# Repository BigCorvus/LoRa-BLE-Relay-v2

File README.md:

# LoRa-BLE-Relay-v2
second version of the nRF52840 and SX126x-based communication device intended to run Meshtastic-
This version is in the testing process. Not confirmed working yet.

See fourm discussion https://meshtastic.discourse.group/t/building-for-nrf52-boards/457/62  

The initial 2.0 version:  

Features are: 
- 110x50mm  
- more ground plane for better LoRa RF performance
- low power consumption in receive mode and Bluetooth active: about 20mA for the 30dbm and 10mA for the 22dbm module version  
- nRF52840 module by Waveshare/HolyIOT with native USB bootloader, broken out NFC pins and good Arduino support (Adafruit Core)  
- Ebyte E22 LoRa Modules based on new Semtech SX126x chipsets for 22 or 30dbm and 915,868,433...Mhz frequency bands. 
- Footprint for both the big and the small LoRa module (the boost converter doesn't need to be assembled if the smaller one is used)  
- SD card slot (same card holder as in the Adafruit Adalogger boards  
- On board buzzer  
- GPS connector breaking out RXD and TXD (JST-SH 4-pin) with high-side power cutting option.   
- Many screen options: usual 128x64 OLEDs via I2C or sunlight-readable and power-efficient ST7565R and UC1701X LCD screens via bitbanged 4 line SPI (see BOM for variants)  
- display headers can be expansion headers  
- 3 nav buttons  
- powered from 1 or 2 parallel unprotected 18650 cells (protection circuitry on board)  
- port for external battery or solar charger for concurrent charging  
- battery temperature monitoring/environmental sensing via BME280  
- USB-C connector
- power management via TI fuel gauge IC with optional programmable power cutting option  (selectable via solder jumper, experimental!) 

To do in next version: reverse polarity protection for batteries.

Installation of the Arduino variant: put the variant.h and .cpp in a folder named LoRaBLERelayV2 which has to be created inside the variants folder of the nrf52 core. There you also have boards.txt which you have to extend by the content of the boards.txt inside this repo.

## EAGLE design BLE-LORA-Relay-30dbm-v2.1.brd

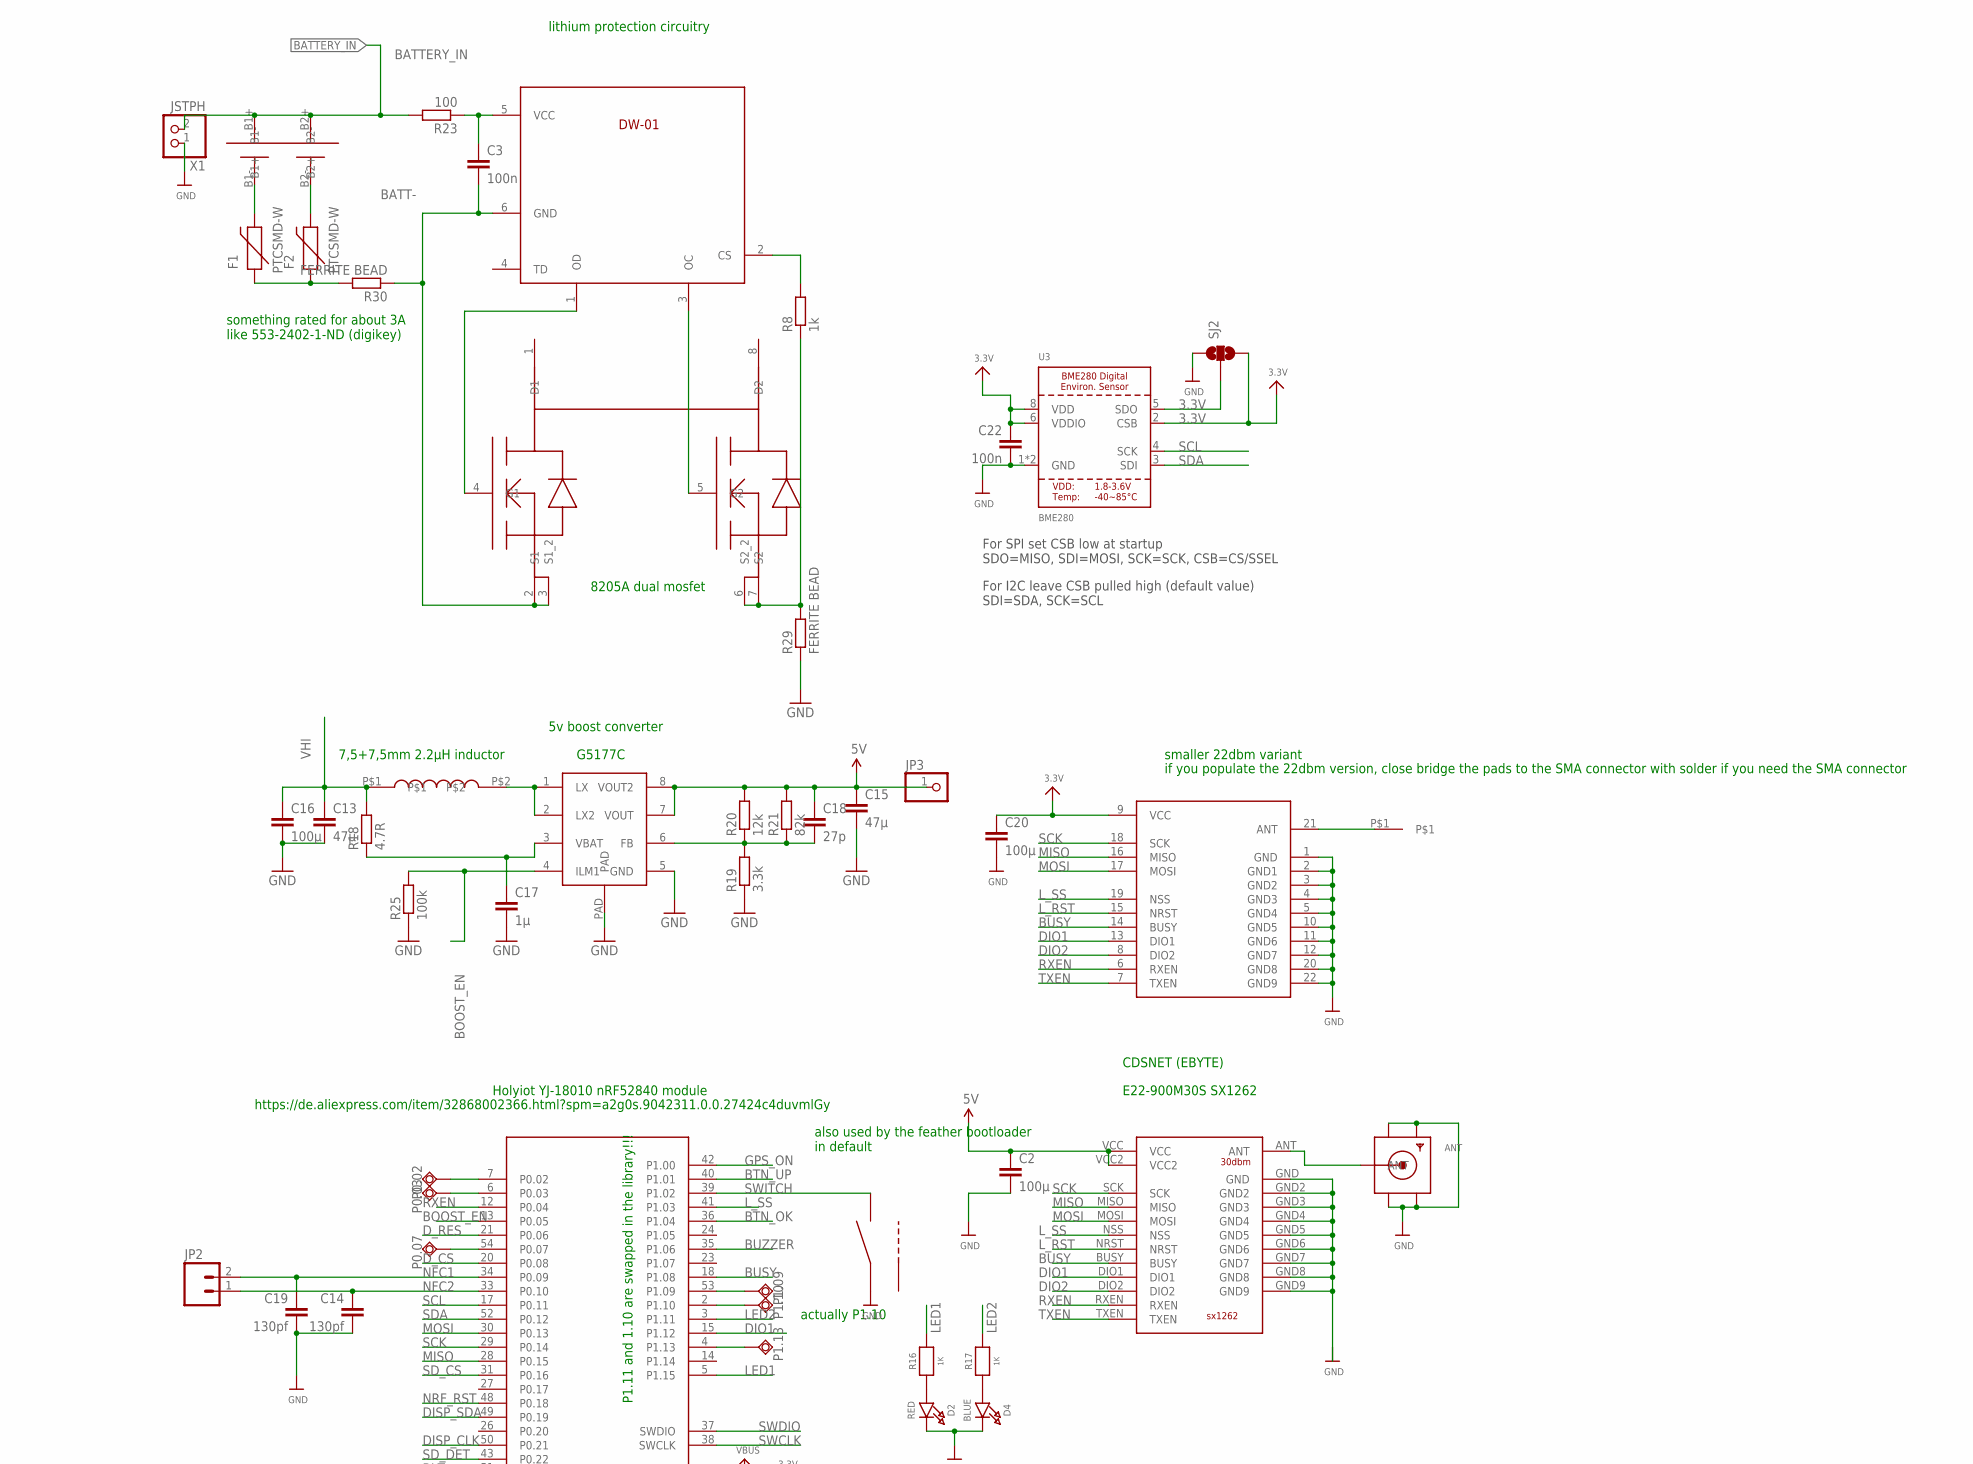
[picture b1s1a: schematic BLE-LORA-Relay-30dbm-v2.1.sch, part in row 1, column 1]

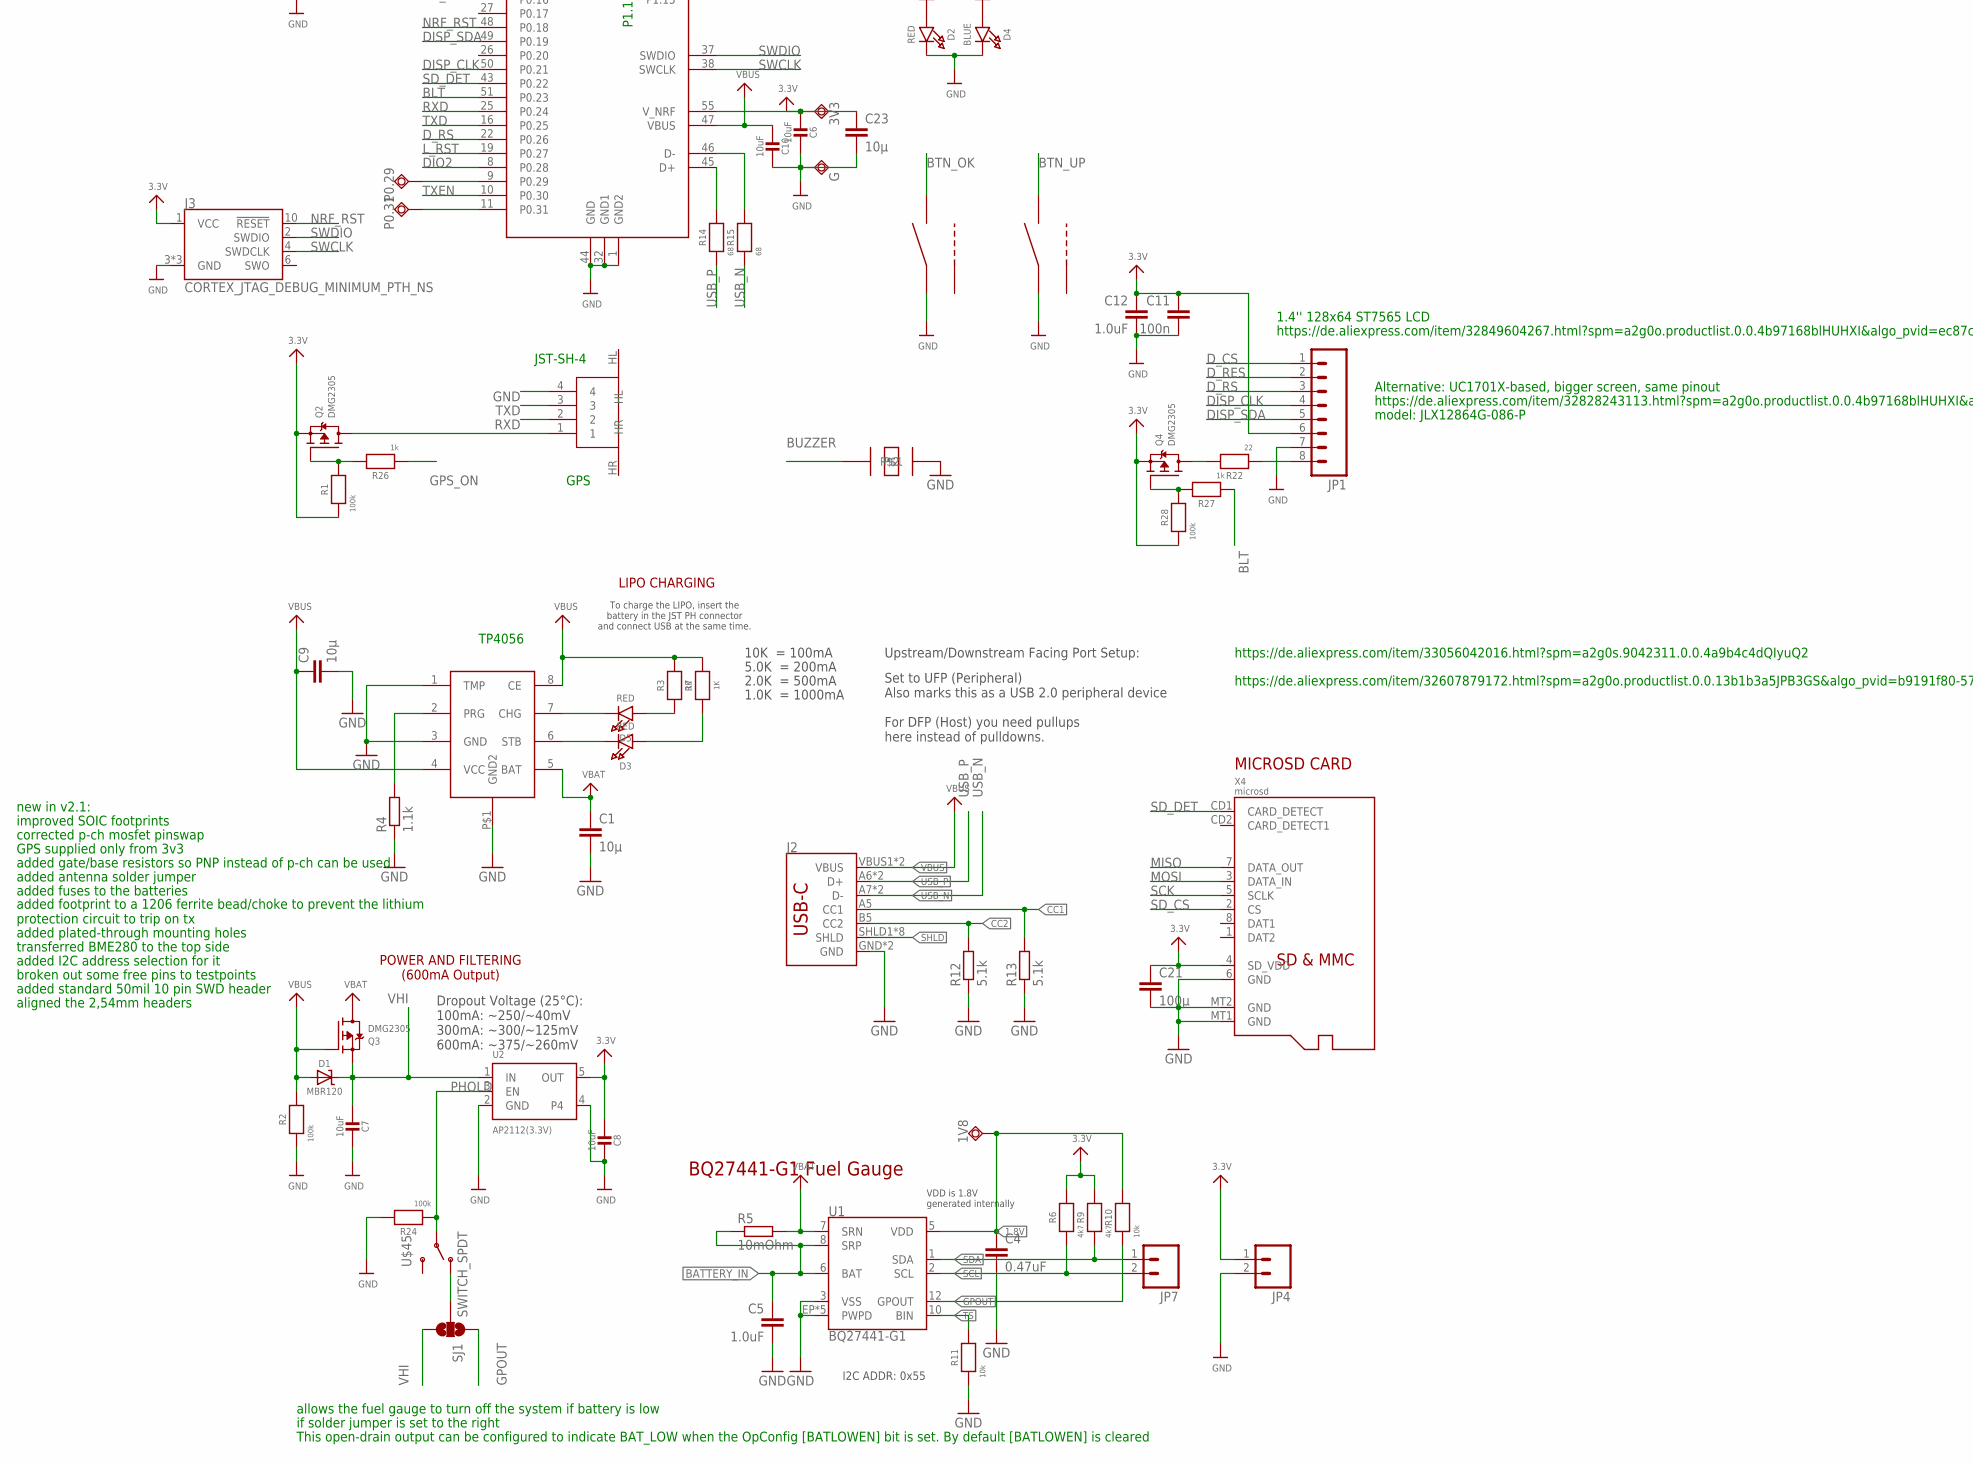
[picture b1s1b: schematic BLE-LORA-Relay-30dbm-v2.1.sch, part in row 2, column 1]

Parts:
1V8, 3V3: TPSQTP13R; TP13R
ANT: SMACONNECTOR_EDGE; SMA_EDGELAUNCH
C1, C9, C23: 10µ; C0805
C2, C16, C20, C21: 100µ; C1206
C3: 100n; C0603
C4: 0.47uF; 0603-CAP
C5, C12: 1.0uF; 0603-CAP
C6, C7, C8, C10: 10uF; 0805-NO
C11, C22: 100n; 0603-CAP
C13, C15: 47µ; C0805
C14, C19: 130pf; 0603-CAP
C17: 1µ; C0603
C18: 27p; C0603
D1: MBR120; SOD-123
D2, D3, D5: RED; CHIPLED_0805_NOOUTLINE
D4: BLUE; CHIPLED_0805_NOOUTLINE
DWN, DWN1, DWN2: LS12T2
F1, F2: PTCSMD-W; PTC-1206-WIDE
G: TPSQTP13R; TP13R
J2: USB_C16PIN; USB-C-16P
J3: CORTEX_JTAG_DEBUG_MINIMUM_PTH_NS; 2X5-PTH-1.27MM-NO_SILK
JP1: M08; 1X08_ROUND
JP2, JP4, JP7: M02PTH; 1X02
JP3: PINHD-1X1; 1X01
P0.02, P0.03, P0.07, P0.29, P0.31, P1.09, P1.10, P1.13: TPSQTP13R; TP13R
Q2, Q3, Q4: DMG2305; SOT23-R
R1, R2, R24, R28: 100k; 0603-NO
R3, R7, R16, R17: 1K; 0603-NO
R4: 1.1k; R0603
R5: 10mOhm; R0805
R6, R9: 4k7; 0603-NO
R8: 1k; R0603
R10, R11: 10k; 0603-NO
R12, R13: 5.1k; R0603
R14, R15: 68; 0603-NO
R18: 4.7R; R0603
R19: 3.3k; R0603
R20: 12k; R0603
R21: 82k; R0603
R22: 22; 0603-NO
R23: 100; R0603
R25: 100k; R0603
R26, R27: 1k; 0603-NO
R29, R30: FERRITE BEAD; R1206
SJ1, SJ2: SOLDERJUMPER_2WAY-OLDS; SJ_3
U1: BQ27441-G1; PDSO-N12
U2: AP2112(3.3V); SOT23-5
U3: BME280
U$2: BUZZER
U$10: 2X18650
U$14: NRF52840; NRF52840MOD
U$15: SX1262-30DBM
U$17: JST-SH-3
U$35: 7.5MM-COIL; 7.5MM_COIL
U$36: SX1292-EBYTE; SX1262_EBYTE
U$38: DW-01; SOT23-6
U$39: G5177C_G5177C; G5177C_SO-08
U$41: SOLDERPAD
U$45: SWITCH_SPDT; KPS-1290
U$46: 8205A; TSSOP8
U$47: TP4056BETTER_TP4056; TP4056BETTER_SO-08
X1: JSTPH; JSTPH2
X4: microsd; MICROSD

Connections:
1.8V: 1V8.TP, C4.1, R10.2, U1.5 (VDD)
3.3V: 3V3.TP, C6.2, C8.2, C11.1, C12.1, C20.1, C21.1, C22.1, C23.1, J3.1 (VCC), JP1.6, JP4.1, Q2.2 (S), Q4.2 (S), R1.1, R6.2, R9.2, R28.1, SJ2.3, U2.5 (OUT), U3.2 (CSB), U3.6 (VDDIO), U3.8 (VDD), U$14.55 (V_NRF), U$36.9 (VCC), X4.4 (SD_VDD)
5V: C2.1, C15.1, C18.1, JP3.1, R20.2, R21.2, U$15.VCC, U$15.VCC2, U$39.7 (VOUT), U$39.8 (VOUT2)
ANT: ANT.P (ANT), U$15.ANT
BATT-: C3.2, R30.1, U$38.6 (GND), U$46.2 (S1), U$46.3 (S1_2)
BATTERY_IN: C5.1, R5.1, R23.2, U1.6 (BAT), U1.8 (SRP), U$10.B1+, U$10.B2+, X1.2
BLT: R27.1, U$14.51 (P0.23)
BOOST_EN: R25.2, U$14.13 (P0.05), U$39.4 (ILM1)
BTN_OK: DWN.1, U$14.36 (P1.04)
BTN_UP: DWN1.1, U$14.40 (P1.01)
BUSY: U$14.18 (P1.08), U$15.BUSY, U$36.14 (BUSY)
BUZZER: U$2.P$1, U$14.35 (P1.06)
CC1: J2.A5 (CC1), R13.2
CC2: J2.B5 (CC2), R12.2
DIO1: U$14.15 (P1.12), U$15.DIO1, U$36.13 (DIO1)
DIO2: U$14.8 (P0.28), U$15.DIO2, U$36.8 (DIO2)
DISP_CLK: JP1.4, U$14.50 (P0.21)
DISP_SDA: JP1.5, U$14.49 (P0.19)
D_CS: JP1.1, U$14.20 (P0.08)
D_RES: JP1.2, U$14.21 (P0.06)
D_RS: JP1.3, U$14.22 (P0.26)
FB: C18.2, R19.2, R20.1, R21.1, U$39.6 (FB)
GGGG: Q4.1 (G), R27.2, R28.2
GND: ANT.GND@1 (GND4), ANT.GND@2 (GND3), ANT.GND@3 (GND2), ANT.GND@4 (GND1), C1.2, C2.2, C4.2, C5.2, C6.1, C7.1, C8.1, C9.2, C10.1, C11.2, C12.2, C13.2, C14.2, C15.2, C16.2, C17.2, C19.2, C20.2, C21.2, C22.2, C23.2, D2.C, D4.C, DWN.2, DWN1.2, DWN2.2, G.TP, J2.GND, J2.GND2 (GND), J3.3 (GND), J3.5 (GND), J3.9 (GND), JP1.7, JP4.2, R2.1, R4.1, R11.1, R12.1, R13.1, R19.1, R24.2, R25.1, R29.1, SJ2.1, U1.3 (VSS), U1.EP (PWPD), U1.EP1 (PWPD), U1.EP2 (PWPD), U1.EP3 (PWPD), U1.EP4 (PWPD), U2.2 (GND), U2.4, U3.1 (GND), U3.7 (GND), U$2.P$2, U$14.1 (GND2), U$14.32 (GND1), U$14.44 (GND), U$15.GND, U$15.GND2, U$15.GND3, U$15.GND4, U$15.GND5, U$15.GND6, U$15.GND7, U$15.GND8, U$15.GND9, U$17.4, U$36.1 (GND), U$36.2 (GND1), U$36.3 (GND2), U$36.4 (GND3), U$36.5 (GND4), U$36.10 (GND5), U$36.11 (GND6), U$36.12 (GND7), U$36.20 (GND8), U$36.22 (GND9), U$39.5 (GND), U$39.PAD, U$47.1 (TMP), U$47.3 (GND), U$47.P$1 (GND2), X1.1, X4.6 (GND), X4.MT1 (GND), X4.MT2 (GND)
GPOUT: R10.1, SJ1.1, U1.12 (GPOUT)
GPS_ON: R26.1, U$14.42 (P1.00)
LED1: R16.2, U$14.5 (P1.15)
LED2: R17.2, U$14.3 (P1.11)
L_RST: U$14.19 (P0.27), U$15.NRST, U$36.15 (NRST)
L_SS: U$14.41 (P1.03), U$15.NSS, U$36.19 (NSS)
MISO: U$14.28 (P0.15), U$15.MISO, U$36.16 (MISO), X4.7 (DATA_OUT)
MOSI: U$14.30 (P0.13), U$15.MOSI, U$36.17 (MOSI), X4.3 (DATA_IN)
unnamed: D5.A, R3.1
unnamed: Q4.3 (D), R22.2
unnamed: SJ1.2, U$45.O
unnamed: JP1.8, R22.1
unnamed: Q2.1 (G), R1.2, R26.2
unnamed: R14.2, U$14.45 (D+)
unnamed: R15.2, U$14.46 (D-)
unnamed: D3.A, R7.1
unnamed: U$38.1 (OD), U$46.4 (G1)
unnamed: R4.2, U$47.2 (PRG)
unnamed: D3.C, U$47.6 (STB)
unnamed: D5.C, U$47.7 (CHG)
unnamed: D2.A, R16.1
unnamed: D4.A, R17.1
unnamed: Q2.3 (D), U$17.1
unnamed: C17.1, R18.1, U$39.3 (VBAT)
unnamed: U$35.P$2, U$39.1 (LX), U$39.2 (LX2)
unnamed: U$38.3 (OC), U$46.5 (G2)
unnamed: C3.1, R23.1, U$38.5 (VCC)
unnamed: U$36.21 (ANT), U$41.P$1
unnamed: F1.2, U$10.B1-
unnamed: F2.2, U$10.B2-
unnamed: R8.2, U$38.2 (CS)
unnamed: R8.1, R29.2, U$46.6 (S2_2), U$46.7 (S2)
unnamed: SJ2.2, U3.5 (SDO)
unnamed: P0.02.TP, U$14.7 (P0.02)
unnamed: P0.03.TP, U$14.6 (P0.03)
unnamed: P1.10.TP, U$14.2 (P1.10)
unnamed: P1.13.TP, U$14.4 (P1.13)
unnamed: P0.31.TP, U$14.11 (P0.31)
unnamed: P0.29.TP, U$14.9 (P0.29)
unnamed: P1.09.TP, U$14.53 (P1.09)
unnamed: P0.07.TP, U$14.54 (P0.07)
unnamed: F1.1, F2.1, R30.2
NFC1: C19.1, JP2.2, U$14.34 (P0.09)
NFC2: C14.1, JP2.1, U$14.33 (P0.10)
NRF_RST: J3.10 (!RESET), U$14.48 (P0.18)
PHOLD: R24.1, U2.3 (EN), U$45.P
RXD: U$14.25 (P0.24), U$17.2
RXEN: U$14.12 (P0.04), U$15.RXEN, U$36.6 (RXEN)
SCK: U$14.29 (P0.14), U$15.SCK, U$36.18 (SCK), X4.5 (SCLK)
SCL: JP7.2, R6.1, U1.2 (SCL), U3.4 (SCK), U$14.17 (P0.11)
SDA: JP7.1, R9.1, U1.1 (SDA), U3.3 (SDI), U$14.52 (P0.12)
SD_CS: U$14.31 (P0.16), X4.2 (CS)
SD_DET: U$14.43 (P0.22), X4.CD1 (CARD_DETECT)
SHLD: J2.SHLD1 (SHLD), J2.SHLD2 (SHLD), J2.SHLD3 (SHLD), J2.SHLD4 (SHLD), J2.SHLD5 (SHLD), J2.SHLD6 (SHLD), J2.SHLD7 (SHLD), J2.SHLD8 (SHLD)
SWCLK: J3.4 (SWDCLK), U$14.38 (SWCLK)
SWDIO: J3.2 (SWDIO), U$14.37 (SWDIO)
SWITCH: DWN2.1, U$14.39 (P1.02)
TS: R11.2, U1.10 (BIN)
TXD: U$14.16 (P0.25), U$17.3
TXEN: U$14.10 (P0.30), U$15.TXEN, U$36.7 (TXEN)
USB_N: J2.A7 (D-), J2.B7 (D-), R15.1
USB_P: J2.A6 (D+), J2.B6 (D+), R14.1
VBAT: C1.1, Q3.3 (D), R5.2, U1.7 (SRN), U$47.5 (BAT)
VBUS: C9.1, C10.2, D1.A, J2.VBUS1 (VBUS), J2.VBUS2 (VBUS), Q3.1 (G), R2.2, R3.2, R7.2, U$14.47 (VBUS), U$47.4 (VCC), U$47.8 (CE)
VHI: C7.2, C13.1, C16.1, D1.C, Q3.2 (S), R18.2, SJ1.3, U2.1 (IN), U$35.P$1

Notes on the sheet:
POWER AND FILTERING (600mA Output)
Dropout Voltage (25°C): 100mA: ~250/~40mV 300mA: ~300/~125mV 600mA: ~375/~260mV
10K = 100mA
5.0K = 200mA
2.0K = 500mA
1.0K = 1000mA
LIPO CHARGING
To charge the LIPO, insert the battery in the JST PH connector and connect USB at the same time.
BQ27441-G1 Fuel Gauge
VDD is 1.8V generated internally
I2C ADDR: 0x55
Holyiot YJ-18010 nRF52840 module
E22-900M30S SX1262
CDSNET (EBYTE)
7,5+7,5mm 2.2µH inductor
G5177C
P1.11 and 1.10 are swapped in the library!!!
GPS
allows the fuel gauge to turn off the system if battery is low
This open-drain output can be configured to indicate BAT_LOW when the OpConfig [BATLOWEN] bit is set. By default [BATLOWEN] is cleared
MICROSD CARD
Set to UFP (Peripheral) Also marks this as a USB 2.0 peripheral device For DFP (Host) you need pullups here instead of pulldowns.
Upstream/Downstream Facing Port Setup:
8205A dual mosfet
lithium protection circuitry
5v boost converter
JST-SH-4
TP4056
if solder jumper is set to the right
smaller 22dbm variant
also used by the feather bootloader in default
For SPI set CSB low at startup SDO=MISO, SDI=MOSI, SCK=SCK, CSB=CS/SSEL
For I2C leave CSB pulled high (default value) SDI=SDA, SCK=SCL
actually P1.10
https://de.aliexpress.com/item/33056042016.html?spm=a2g0s.9042311.0.0.4a9b4c4dQIyuQ2
https://de.aliexpress.com/item/32868002366.html?spm=a2g0s.9042311.0.0.27424c4duvmlGy
https://de.aliexpress.com/item/32607879172.html?spm=a2g0o.productlist.0.0.13b1b3a5JPB3GS&algo_pvid=b9191f80-57f7-4ba1-a376-d5b7fd01a70f&algo_expid=b9191f80-57f7-4ba1-a376-d5b7fd01a70f-25&btsid=0ab50f4915950751178702682eb47a&ws_ab_test=searchweb0_0,searchweb201602_,searchweb201603_
1.4'' 128x64 ST7565 LCD
https://de.aliexpress.com/item/32849604267.html?spm=a2g0o.productlist.0.0.4b97168blHUHXI&algo_pvid=ec87ccf3-48e0-4d00-a283-bb0252849e1b&algo_expid=ec87ccf3-48e0-4d00-a283-bb0252849e1b-7&btsid=0ab6fb8315950916206164907e80e8&ws_ab_test=searchweb0_0,searchweb201602_,searchweb201603_
https://de.aliexpress.com/item/32828243113.html?spm=a2g0o.productlist.0.0.4b97168blHUHXI&algo_pvid=ec87ccf3-48e0-4d00-a283-bb0252849e1b&algo_expid=ec87ccf3-48e0-4d00-a283-bb0252849e1b-8&btsid=0ab6fb8315950916206164907e80e8&ws_ab_test=searchweb0_0,searchweb201602_,searchweb201603_

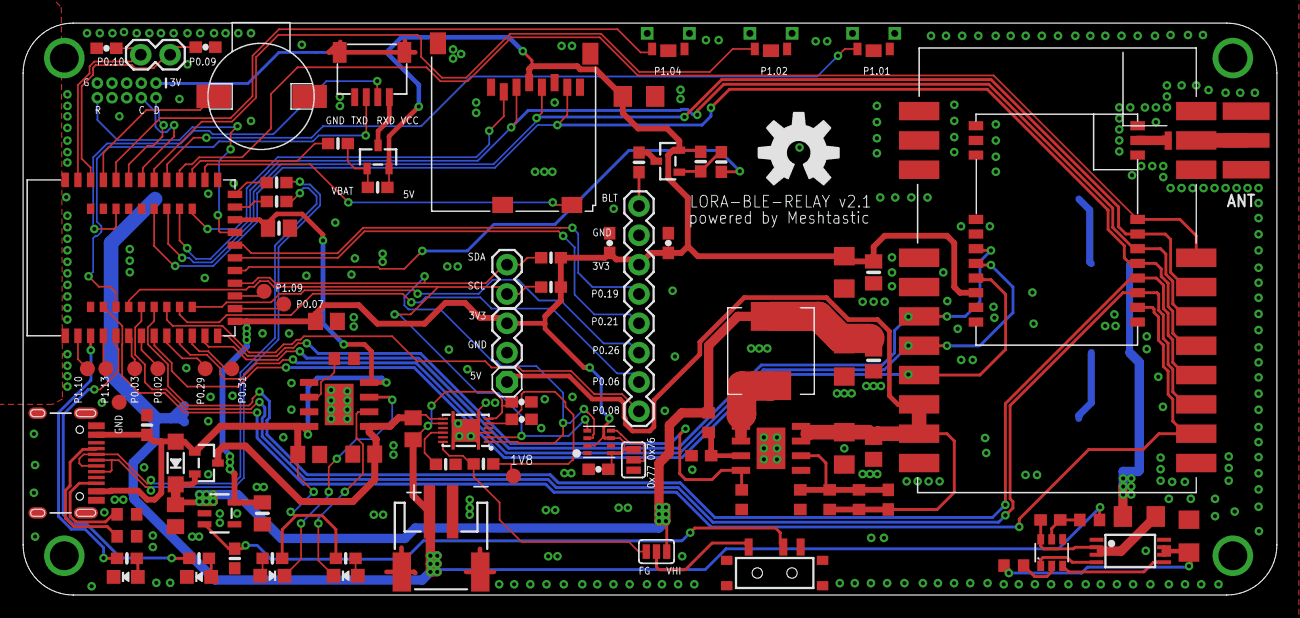
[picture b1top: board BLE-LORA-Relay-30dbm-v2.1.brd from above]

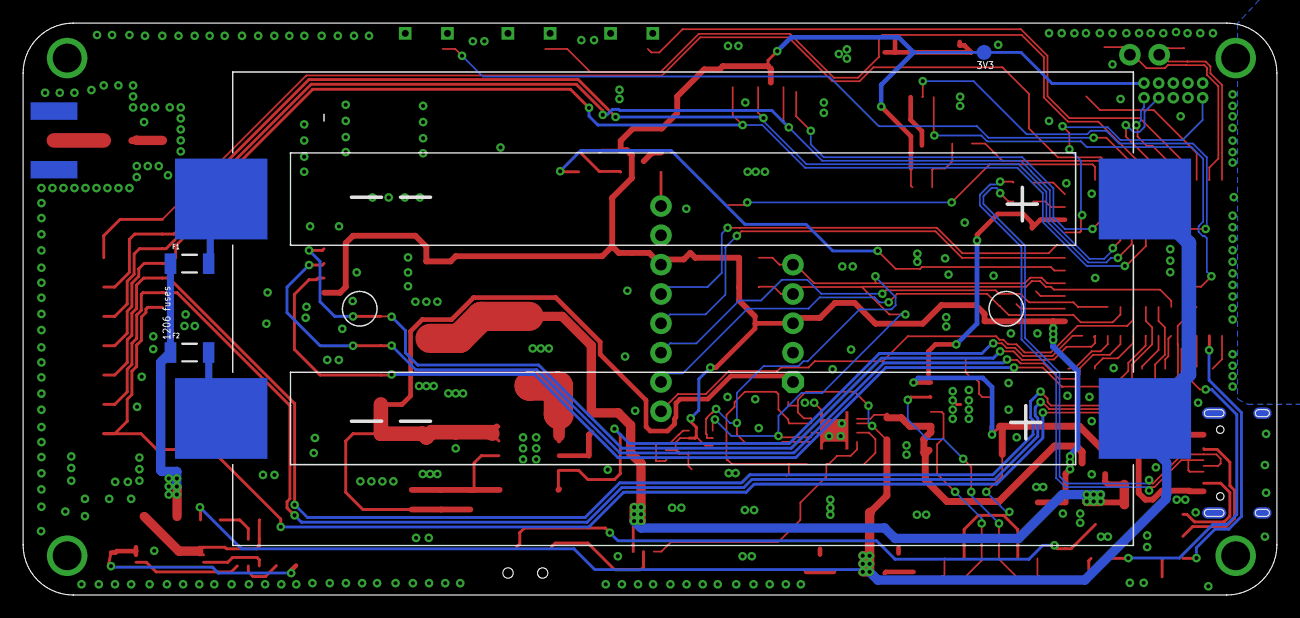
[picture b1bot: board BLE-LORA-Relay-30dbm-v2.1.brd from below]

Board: 2 copper layers, 108.6 x 49.5 mm, 106 parts (4 on the bottom side), 89 nets.

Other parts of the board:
U$7: OSHW-LOGO-L

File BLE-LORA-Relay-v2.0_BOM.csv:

Qty;Value;Device;Package;Parts;Description;Search Keywords, remarks;Buying URL
3;;M02PTH;1X02;JP2, JP4, JP7;"Standard 2-pin 0.1 header. Use with""";;
1;;M08;1X08_ROUND;JP1;Header 8;;
1;;PINHD-1X1;1X01;JP3;"Pin header 1x1 for 0.1 spacing""";;
1;;SMACONNECTOR_EDGE;SMA_EDGELAUNCH;ANT;SMA Connector;;
1;;USB_C16PIN;USB-C-16P;J2;USB Type C 16Pin Connector;USB Type c 16 pin;https://de.aliexpress.com/item/33056042016.html?spm=a2g0s.90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
1;0.47uF;CAP0603-CAP;0603-CAP;C4;Capacitor;;
3;1.0uF;1.0UF-16V-10%(0603);0603-CAP;C5, C12, C17;CAP-00868;;
1;1.1k;R-EU_R0603;R0603;R4;RESISTOR, European symbol;;
1;100R;R-EU_R0603;R0603;R23;RESISTOR, European symbol;;
5;100k;R-EU_R0603;R0603;R25, R1, R2, R24, R28;RESISTOR, European symbol;;
3;100n;1.0UF-16V-10%(0603);0603-CAP;C11, C22, C3;CAP-00868;;
4;100µ;C-EUC1206;C1206;C2, C16, C20, C21;CAPACITOR, European symbol;;
2;10k;RESISTOR_0603_NOOUT;0603-NO;R10, R11;Resistors;;
1;10mOhm;R-EU_R0805;R0805;R5;RESISTOR, European symbol;;
9;10...47uF;CAP_CERAMIC0805-NOOUTLINE;0805-NO;C13, C15, C6, C7, C8, C10, C1, C9, C23;Ceramic Capacitors;;
1;12k;R-EU_R0603;R0603;R20;RESISTOR, European symbol;;
2;130pf;1.0UF-16V-10%(0603);0603-CAP;C14, C19;CAP-00868;;
7;1K;RESISTOR_0603_NOOUT;0603-NO;R3, R7, R16, R17, R8, R26, R27;Resistors;;
1;22R;RESISTOR_0603_NOOUT;0603-NO;R22;Resistors;;
1;27p;C-EUC0603;C0603;C18;CAPACITOR, European symbol;;
1;2X18650;2X18650;2X18650;U$10;;single or dual 18650 holder, surface mount;https://de.aliexpress.com/item/4000868337607.html?spm=a2g0o.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,searchweb201602_,searchweb201603_
1;3.3k;R-EU_R0603;R0603;R19;RESISTOR, European symbol;;
1;4.7R;R-EU_R0603;R0603;R18;RESISTOR, European symbol;;
4;5.1k;R-EU_R0603;R0603;R12, R13, R6, R9;RESISTOR, European symbol;;
2;68R;RESISTOR_0603_NOOUT;0603-NO;R14, R15;Resistors;;
1;7.5MM-COIL;7.5MM-COIL;7.5MM_COIL;U$35;;;
1;8205A;8205A;TSSOP8;U$46;Dual Mosfet;;
1;82k;R-EU_R0603;R0603;R21;RESISTOR, European symbol;;
1;AP2112(3.3V);VREG_SOT23-5;SOT23-5;U2;SOT23-5 Fixed Voltage Regulators;;
1;BLUE;LED0805_NOOUTLINE;CHIPLED_0805_NOOUTLINE;D4;LED;;
1;BME280;BME280;BME280;U3;BME280 - Environmental Sensor (I2C + SPI);;
1;BQ27441-G1;BQ27441-G1;PDSO-N12;U1;Fuel gauge IC;;
1;BUZZER;BUZZER;BUZZER;U$2;;9032 9,0 x 3.2 magnetic buzzer;https://de.aliexpress.com/item/4000148853278.html?spm=a2g0o.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,searchweb201602_,searchweb201603_
3;DMG2305;MOSFET-P;SOT23-R;Q2, Q3, Q4;P-Channel Mosfet;;
1;DW-01;DW-01;SOT23-6;U$38;Lithium protection IC;;
1;G5177C;G5177C;SO-08;U$41;Synchronous boost converter IC;;
1;JST-SH-3;JST-SH-3;JST-SH-3;U$17;actually, surface mount 4-pin 1mm connector for GPS: JST-SH4;;
1;JSTPH;CON_JST_PH_2PIN;JSTPH2;X1;JST 2-Pin Right-Angle Connector;;
3;LS12T2;LS12T2;LS12T2;DWN, DWN1, DWN2;Pushbutton;Digikey 1642-1312-1-ND;
1;MBR120;DIODE-SCHOTTKYSOD-123;SOD-123;D1;;;
1;NRF52840;NRF52840;NRF52840MOD;U$14;Manufactued by HolyIOT or waveshare;;https://de.aliexpress.com/item/32868002366.html?spm=a2g0s.90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
3;RED;LED0805_NOOUTLINE;CHIPLED_0805_NOOUTLINE;D2, D3, D5;LED;;
1;SWITCH_SPDT;SWITCH_SPDT;KPS-1290;U$45;SWCH-10651;SPDT MSK-12C02;https://de.aliexpress.com/item/32856542440.html?spm=a2g0o.pr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,searchweb201602_,searchweb201603_
1;SX1262-30DBM;SX1262-30DBM;SX1262-30DBM;U$15;1W LoRa module by ebyte;search ebyte on aliexpress and get the E22 variants which can contain either a SX1262 or SX1268 and come in 22dbm or 30dbm variants;
1;SX1292-EBYTE;SX1292-EBYTE;SX1262_EBYTE;U$36;22dbm LoRa module by ebyte;;
1;TP4056;TP4056;SO-08;U$3;Lithium charger;;
6;TPSQTP13R;TPSQTP13R;TP13R;1V8, 3V3, G, RST, SWC, SWD;Test pad;;
1;microsd;MICROSD;MICROSD;X4;MicroSD/Transflash Card Holder with SPI pinout;;https://de.aliexpress.com/item/32607879172.html?spm=a2g0o.pr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,searchweb201602_,searchweb201603_
1;1.4 inch ST7565 LCD 128x64;;;;;preferred variant;https://de.aliexpress.com/item/32849604267.html?spm=a2g0o.pr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,searchweb201602_,searchweb201603_
; Alternative: UC1701X-based, bigger screen, same pinout, model: JLX12864G-086-P;;;;;;https://de.aliexpress.com/item/32828243113.html?spm=a2g0o.pr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,searchweb201602_,searchweb201603_
2;;Ferrite Bead 3A;1206;R29, 30;;553-2402-1-ND Digikey;

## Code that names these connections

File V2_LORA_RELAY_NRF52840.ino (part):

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  Also implements all the housekeeping such as the BQ27441 fuel gauge, ST7735 LCD and buttons.
  If using the Feather nrf52840 express bootloader the SWITCH button can be used to enter bootloader mode if pressed on startup. LED1 is the bootloader LED
  Note that you need to modify the variant.h and variant.cpp as described below in order to get software acces to certain pins. See the core documentation for more info on where to find those files.
  Also note that the PHOLD pin was separated from the rest of the circuit by cutting a trace on the PCB between the P0.05 pad on the nrf52840 module and the via next to it so the power latching circuit is not used.
  This will be corrected in an upcoming version of the design files.

*********************************************************************/
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unsigned int soc = 0;


#define DIO1 (44)//P1.12
#define DIO2 (28)//P0.28
#define TXEN (30)//P0.30
#define RXEN (4)//P0.04
#define L_SS (35)//P1.03 
#define BUSY (40)//P1.08
#define L_RST (27)//P0.27

#define BTN_UP (33)//P1.01
#define BTN_DN (36)//P1.04 
#define SWITCH (34)//P1.02

#define LED2 (42)//P1.10
#define LED1 (47)//P1.15
#define PIEZO (38)//P1.06 

#define D_RES (6)//P0.06
#define D_CS (8)//P0.08
#define BLT (23)//P0.23
#define D_RS (26)//P0.26
#define DISP_SDA (19)//P0.19
#define DISP_CLK (21)//P0.21

#define SD_DET (22) //P0.22
#define SD_CS (16) //0.16

#define BOOST_EN (5) //P0.05
#define GPS_ON (32)//P1.00


// BLE Service
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
// SX1262 has the following connections:
// NSS pin:
// DIO1 pin:
// NRST pin:  <--? actually DIO2
// BUSY pin:

SX1262 lora = new Module(L_SS, DIO1, -1, BUSY);
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  setupBQ27441();
  soc = lipo.soc();  // Read state-of-charge (%)

  pinMode(LED1, OUTPUT);
  pinMode(LED2, OUTPUT);
  pinMode(BLT, OUTPUT); //LOW means ON
  pinMode(BOOST_EN, OUTPUT); //LOW means ON
  pinMode(GPS_ON, OUTPUT);
  pinMode(PIEZO, OUTPUT);

  pinMode(L_RST, OUTPUT);
  pinMode(TXEN, OUTPUT);
  pinMode(RXEN, OUTPUT);

  pinMode(BTN_UP, INPUT_PULLUP);
  pinMode(SWITCH, INPUT_PULLUP);
  pinMode(BTN_DN, INPUT_PULLUP);

  pinMode(SD_DET, INPUT);

  digitalWrite(BOOST_EN, HIGH);

  delay(1000);
  digitalWrite(BLT, LOW);
  pinMode(GPS_ON, LOW);
  delay(3000);
  digitalWrite(BLT, HIGH);
  pinMode(GPS_ON, HIGH);


  
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
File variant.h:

 /*
  Copyright (c) 2014-2015 Arduino LLC.  All right reserved.
  Copyright (c) 2016 Sandeep Mistry All right reserved.
  Copyright (c) 2018, Adafruit Industries (adafruit.com)

  This library is free software; you can redistribute it and/or
  modify it under the terms of the GNU Lesser General Public
  License as published by the Free Software Foundation; either
  version 2.1 of the License, or (at your option) any later version.
  This library is distributed in the hope that it will be useful,
  but WITHOUT ANY WARRANTY; without even the implied warranty of
  MERCHANTABILITY or FITNESS FOR A PARTICULAR PURPOSE.
  See the GNU Lesser General Public License for more details.
  You should have received a copy of the GNU Lesser General Public
  License along with this library; if not, write to the Free Software
  Foundation, Inc., 51 Franklin St, Fifth Floor, Boston, MA  02110-1301  USA
*/

#ifndef _VARIANT_LoRaBLERelayV2_
#define _VARIANT_LoRaBLERelayV2_

/** Master clock frequency */
#define VARIANT_MCK       (64000000ul)

#define USE_LFXO      // Board uses 32khz crystal for LF
// define USE_LFRC    // Board uses RC for LF

/*----------------------------------------------------------------------------
 *        Headers
 *----------------------------------------------------------------------------*/

#include "WVariant.h"

#ifdef __cplusplus
extern "C"
{
#endif // __cplusplus

// Number of pins defined in PinDescription array
#define PINS_COUNT           (48)
#define NUM_DIGITAL_PINS     (48)
#define NUM_ANALOG_INPUTS    (6) // A6 is used for battery, A7 is analog reference
#define NUM_ANALOG_OUTPUTS   (0)

// LEDs
#define PIN_LED1             (47)
#define PIN_LED2             (42)
//#define PIN_NEOPIXEL         (8)

#define LED_BUILTIN          PIN_LED1
#define LED_CONN             PIN_LED2

#define LED_RED              PIN_LED1
#define LED_BLUE             PIN_LED2

#define LED_STATE_ON         1         // State when LED is lit

/*
 * Buttons
 */
#define PIN_BUTTON1             (34)

/*
 * Analog pins
 */
#define PIN_A0               (3)
#define PIN_A1               (4)
#define PIN_A2               (28)
#define PIN_A3               (29)
#define PIN_A4               (30)
#define PIN_A5               (31)
#define PIN_A6               (0xff)
#define PIN_A7               (0xff)

static const uint8_t A0  = PIN_A0 ;
static const uint8_t A1  = PIN_A1 ;
static const uint8_t A2  = PIN_A2 ;
static const uint8_t A3  = PIN_A3 ;
static const uint8_t A4  = PIN_A4 ;
static const uint8_t A5  = PIN_A5 ;
static const uint8_t A6  = PIN_A6 ;
static const uint8_t A7  = PIN_A7 ;
#define ADC_RESOLUTION    14

// Other pins
#define PIN_AREF           31
//#define PIN_VBAT           PIN_A6
#define PIN_NFC1           (9)
#define PIN_NFC2           (10)

static const uint8_t AREF = PIN_AREF;

/*
 * Serial interfaces
 */
#define PIN_SERIAL1_RX       (24)
#define PIN_SERIAL1_TX       (25)

/*
 * SPI Interfaces
 */
#define SPI_INTERFACES_COUNT 1

#define PIN_SPI_MISO         (15)
#define PIN_SPI_MOSI         (13)
#define PIN_SPI_SCK          (14)

static const uint8_t SS   = (35);
static const uint8_t MOSI = PIN_SPI_MOSI ;
static const uint8_t MISO = PIN_SPI_MISO ;
static const uint8_t SCK  = PIN_SPI_SCK ;

/*
 * Wire Interfaces
 */
#define WIRE_INTERFACES_COUNT 1

#define PIN_WIRE_SDA         (12)
#define PIN_WIRE_SCL         (11)



// On-board QSPI Flash
//#define EXTERNAL_FLASH_DEVICES   GD25Q16C
//#define EXTERNAL_FLASH_USE_QSPI

#ifdef __cplusplus
}
#endif

/*----------------------------------------------------------------------------
 *        Arduino objects - C++ only
 *----------------------------------------------------------------------------*/

#endif

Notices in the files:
parts and their libraries:
microbuilder: This work is placed in the public domain, and may be freely used for commercial and non-commercial work with the following conditions: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
SparkFun-Capacitors: Licensing: Creative Commons ShareAlike 4.0 International - https://creativecommons.org/licenses/by-sa/4.0
